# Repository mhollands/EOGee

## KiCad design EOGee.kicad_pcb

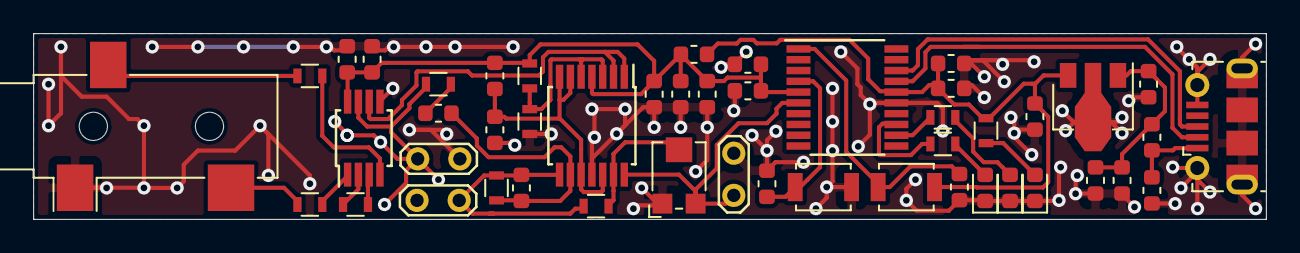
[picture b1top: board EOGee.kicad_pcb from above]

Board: 2 copper layers, 74.3 x 11.2 mm, 48 parts (0 on the bottom side), 29 nets.

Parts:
C101, C108: 0.1uF; C_0603_1608Metric
C102, C107, C117, C118: 100nF; C_0603_1608Metric
C103, C115: 10nF; C_0603_1608Metric
C104, C109, C119: 4.7uF; C_0603_1608Metric
C105, C106, C110, C113: 10uF; C_0603_1608Metric
C111, C112, C116: 1uF; C_0603_1608Metric
C114: 560pF; C_0603_1608Metric
D101, D102, D103: LED; LED_0603_1608Metric
J101: USB_B_Micro; USB_Micro-B_Molex-105017-0001
J102: AudioJack3; Jack_3.5mm_CUI_SJ-3523-SMT_Horizontal
L101, L102: BK0603HS330-T; L_0603_1608Metric
R101: 16k; R_0603
R102, R103: 47k; R_0603
R104, R105, R106: 10k; R_0603
R107: 2.2M; R_0603
R108: 1k; R_0603
R109: 10k; R_0603_1608Metric
R110, R111, R112: 750; R_0603
RV101: R_POT; Potentiometer_Bourns_TC33X_Vertical
SW101, SW102: SW_Push_45deg; SW_SPST_B3U-1000P
TP101, TP102, TP103: TestPoint_2Pole; TestPoint_2Pads_Pitch2.54mm_Drill0.8mm
U101: LMV324; TSSOP-14_4.4x5mm_P0.65mm
U102: AD8226ARMZ; MSOP-8_3x3mm_P0.65mm
U103: AP2210; SOT-89-3
U105: STM32F042F4Px; TSSOP-20_4.4x6.5mm_P0.65mm

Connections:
+3.3VA: C101.1, C102.1, C104.1, C105.1, C108.1, C110.1, C115.1, C116.1, L101.2, R104.1, U101.4, U102.8, U105.5
+3V3: C112.1, C117.1, C119.1, L101.1, R112.1, SW101.1, U103.3, U105.16
/USB_DM: J101.2, U105.17
/USB_DP: J101.3, U105.18
GND: C101.2, C102.2, C103.2, C104.2, C106.2, C107.2, C108.2, C109.2, C110.2, C111.2, C112.2, C115.2, C116.2, C117.2, C118.2, C119.2, D101.1, D102.1, D103.1, J101.5, J101.6, J102.S, R105.2, R109.2, RV101.1, SW102.1, TP101.2, TP102.2, TP103.2, U101.11, U102.5, U103.2, U105.15
unnamed: C103.1, J101.1, L102.1
unnamed: C105.2, C106.1, U101.6, U101.7, U101.10, U101.12
unnamed: C107.1, C109.1, C111.1, L102.2, U103.1
unnamed: C113.1, C114.2, R107.2, U101.9
unnamed: C113.2, R106.1
unnamed: C114.1, R107.1, R108.2, TP102.1, U101.8
unnamed: C118.1, SW102.2, U105.4
unnamed: D101.2, R110.2
unnamed: D102.2, R111.2
unnamed: D103.2, R112.2
unnamed: J102.R, R103.2
unnamed: J102.T, R102.2
unnamed: R101.1, U102.2
unnamed: R101.2, U102.3
unnamed: R102.1, U102.1
unnamed: R103.1, U102.4
unnamed: R104.2, R105.1, U101.3, U101.5
unnamed: R106.2, TP101.1, U102.7
unnamed: R108.1, RV101.2, U101.13
unnamed: R109.1, SW101.2, U105.1
unnamed: R110.1, U105.13
unnamed: R111.1, U105.12
unnamed: RV101.3, TP103.1, U101.14, U105.6
unnamed: U101.1, U101.2, U102.6

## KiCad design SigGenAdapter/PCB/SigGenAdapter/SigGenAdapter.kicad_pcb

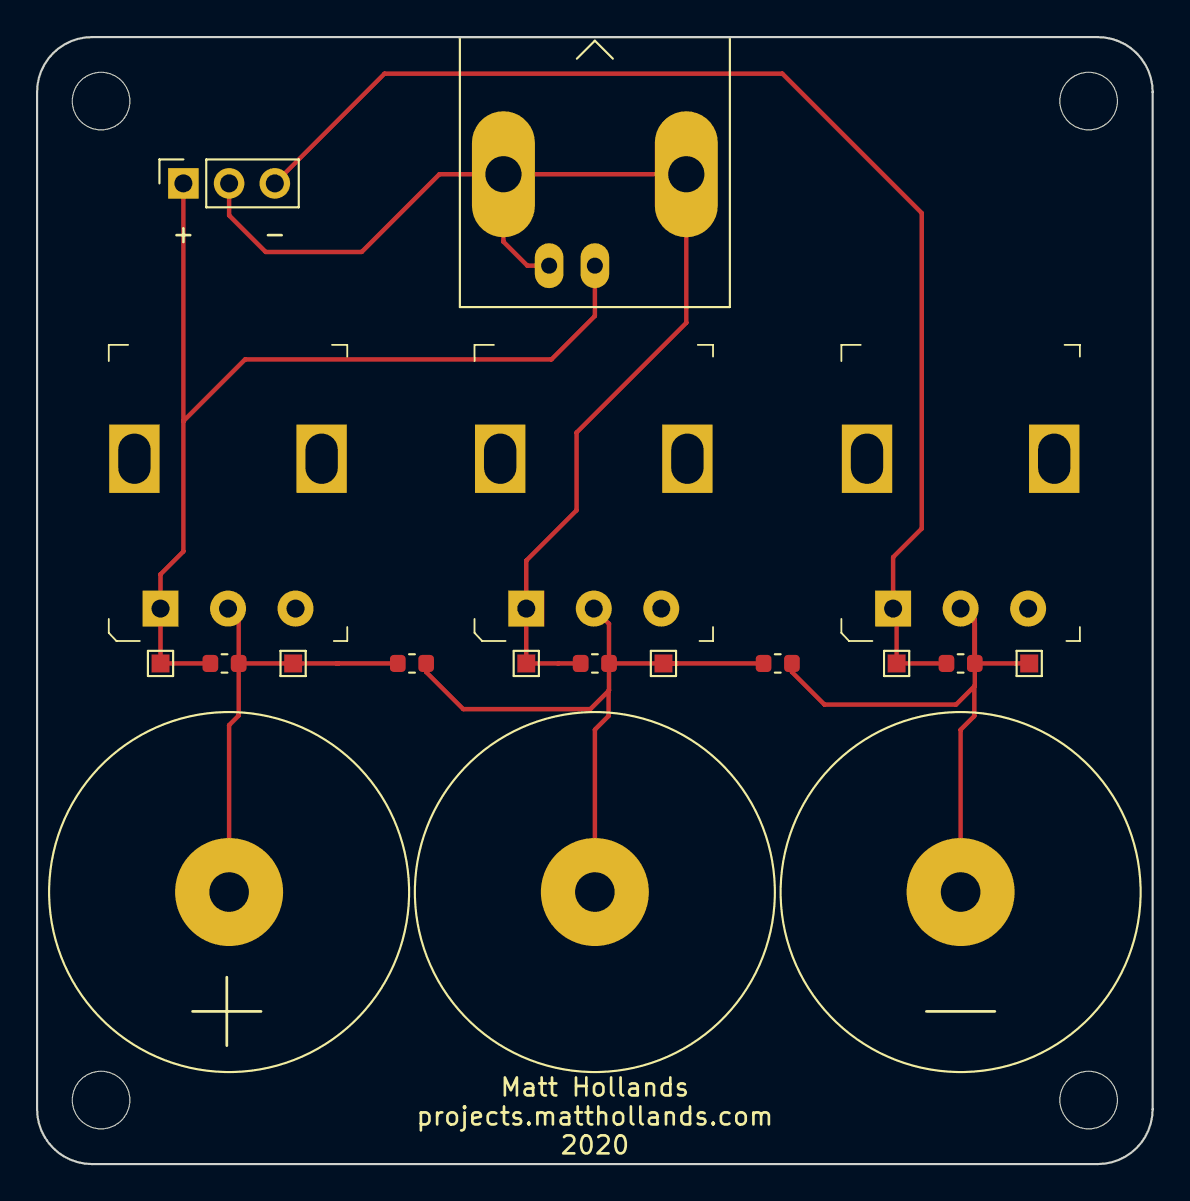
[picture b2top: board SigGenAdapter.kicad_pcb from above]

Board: 2 copper layers, 62.0 x 62.6 mm, 23 parts (0 on the bottom side), 6 nets.

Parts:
H1, H2, H3, H4: MountingHole; MountingHole_3.2mm_M3
J1: Conn_Coaxial; BNC_Amphenol_B6252HB-NPP3G-50_Horizontal
J2: Conn_01x03; PinSocket_1x03_P2.54mm_Vertical
J3, J4, J5: Screw_Terminal_01x01; MountingHole_2.2mm_M2_Pad
R1, R2, R3, R4, R5: R; R_0603_1608Metric
RV1, RV2, RV3: R_POT; Potentiometer_P120PK-Y25BR10K
TP1, TP2, TP3, TP4, TP5, TP6: TestPoint; TestPoint_Pad_1.0x1.0mm

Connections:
/GND: J1.2, J2.2, R3.2, RV3.1, TP1.1
/GND_R: J4.1, R3.1, R4.1, R5.2, RV3.2, TP2.1
/SIGNAL_N: J2.3, R2.2, RV2.1, TP4.1
/SIGNAL_N_R: J5.1, R2.1, R5.1, RV2.2, TP6.1
/SIGNAL_P: J1.1, J2.1, R1.2, RV1.1, TP3.1
/SIGNAL_P_R: J3.1, R1.1, R4.2, RV1.2, TP5.1
